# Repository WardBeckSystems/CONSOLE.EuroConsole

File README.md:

# EuroConsole

**A modular analog mixing console in Eurorack: Ward-Beck Systems circuits, digitally controlled, wired with Quad Twisted Pair.**

**Start here:** [`index.html`](index.html) walks through the whole console step by step. [`EDITOR/index.html`](EDITOR/index.html) builds your configuration as a KiCad schematic.

EuroConsole grows out of the 2016|49 *Digitally Controlled Analog Surround Sound Panner* (DCASSP), built at APK audio and Ward-Beck Systems as a Seneca College technology project. That prototype showed one idea: **the audio stays analog, the controls go digital**. Every control a mixer touches (encoders, buttons, faders, LEDs) is read by a microcontroller. The microcontroller sets digitally controlled analog parts, such as the Maxim DS1882 log-taper audio potentiometers, which do the actual work on the signal. Because the panel never carries audio, the controls can move, light up, recall and be driven remotely, and the signal path keeps the sound of the Ward-Beck circuits.

EuroConsole turns that prototype into a whole console, built from 3U Eurorack modules. The first build is the **C1616**:

| Part | What it is |
|---|---|
| **C1616 console** | 16 input channels (B300 Brain + F300 Fader strips) feeding **16 summing amplifiers**, in 4 rows of 6 modules |
| **Input** | M480B input module: the channel's mic/line front end |
| **4-input summing console** | one row: 4 × RJ45 QTP in (all 16 channels) → 4 summing amps, each with an insert point |
| **Processing** | EQ, compressor, de-esser, gate: patch into any insert |
| **Patch bay** | QTP patch bay module: inserts and buses on RJ45, normalled through |
| **Big VU Meter** (RD87) | the console's meter: the RD87 stereo Neopixel LED tower and its driver (REV 5, 2021\|54), plus moving-coil VU panels |

Everything connects with **QTP (Quad Twisted Pair)**: four balanced analog channels on one RJ45 / CAT5e cable, in the colour order **SUN, SKY, GRASS, EARTH**.

---

## How it fits together

```mermaid
flowchart LR
  subgraph CH["C1616: 16 channel strips"]
    direction TB
    B["B300 Brain<br/>input select · 4 aux · ESP32-S3"] --- F["F300 Fader<br/>POS pan · ONLY · SEL · fader · CH ON"]
  end
  IN["16 inputs<br/>(4 × QTP RJ45)"] --> M480["M480B input modules"] --> CH
  PB["QTP patch bay"] -.-|"normalled inserts and buses"| INS
  CH -->|"16 channels = 4 × QTP, to every row"| SUM
  subgraph SUM["Summing: 4 rows × (4 summing amps + insert + Big VU) = 16 summing amps"]
    direction TB
    Q["each row: 4 × RJ45 QTP in"] --> BUS["4 summing amps per row<br/>SUN · SKY · GRASS · EARTH"]
    BUS --> INS["insert point per bus<br/>send / return"]
  end
  INS <-->|"QTP send / return"| PROC
  subgraph PROC["Processing (any insert)"]
    direction TB
    EQ["EQ"] ~~~ COMP["Compressor"] ~~~ DES["De-esser"] ~~~ GATE["Gate"]
  end
  INS --> OUT["4 bus outputs (QTP)"]
  OUT --> DRV["Big VU Meter driver<br/>line in · MCU"] --> VU["Big VU Meter<br/>2 × 57 Neopixels"]
```

### Signal rules

- **Audio is analog and balanced end to end**: THAT 1246 line receivers in, THAT 1646 line drivers out. The 2016|49 prototype used these on every board.
- **Control is digital**: one ESP32-S3 per channel strip reads the panel and sets the gain parts. The modules talk to each other over I2C on the Eurorack bus, and the console talks to the outside world over the network. The 2016|49 prototype used Ethernet and the HUI protocol, run from an Arduino Mega.
- **Every interconnect is QTP**: one RJ45 carries four channels, so 16 outputs need only four cables. A QTP pair is also the insert send / return.

---

## 1. The C1616 console (16 × 16): channel strip = B300 + F300

**C1616** = 16 input channels × 16 summing amplifiers.

Each channel strip is two 6HP × 3U modules from the *HUI front panel REV 4.1* drawing ([DXF](MECHANICAL/HUI%20front%20panel%20REV%204.1.dxf)):

| B300 **Brain** (left) | F300 **Fader** (right) |
|---|---|
| INPUT LED and SEL button | **POS** encoder: position in the surround field (L · C · R · Ls · Rs) |
| SUN / SKY / GRASS / EARTH: four auxiliary controls, each with an encoder, a Neopixel and a push-button | **ONLY**: solo, isolate and cue |
| carries the channel's microcontroller | **SEL**: select, which draws attention to the channel |
| | 60 mm linear **fader** (Bourns PTA6043): channel level |
| | **CH ON**: channel on |

**Panning (from the 2016|49 theory of operation).** The POS encoder indexes a table of DS1882 settings, one per speaker, at 1 dB per step. Each speaker peaks at 63–64 steps, and neighbouring speakers cross at 48 steps (16 dB down):

```
{64,0,0,0,0} {48,48,0,0,0} {0,63,0,0,0} {0,48,48,0,0} {0,0,63,0,0} {0,0,48,48,0} {0,0,0,64,0} {0,0,0,48,48} {0,0,0,0,63}
```

The fader scales the looked-up row to a percentage. At power-up, every pot starts at full mute.

**C1616.** 16 input channels feed 16 summing amplifiers. The 16 channels leave the strips on four QTP cables (4 channels each), and every summing row receives all four. 16 strips × 12HP = 192HP, which is three rows of 84HP.

---

## 2. Summing: 4 rows of 6 = 16 summing amplifiers

The summing side is **4 rows of 6 modules**. Each row is one **4-input summing console**:

| Slot | Module |
|---|---|
| 1–4 | **summing amplifiers**: the row's four buses, SUN · SKY · GRASS · EARTH. All 16 channels arrive on the row's 4 × RJ45 QTP inputs |
| 5 | **insert / patch**: an insert send / return for each of the row's four buses (QTP) |
| 6 | **Big VU (RD87)**: meters the row's four buses |

4 rows × 4 = **16 summing amplifiers**: 16 inputs × 16 summing buses. Each bus has an **insert point** and leaves on a QTP output. *Slots 5 and 6 are provisional; the layout of 4 summing amps + 2 per row is set.* Big VU REV 5 shows two bars, so the row needs a 4-bar version, or two towers.

- **Summing amplifier:** Ward-Beck [M450](https://github.com/WardBeckSystems/MODULES.AMPLIFIERS.M450-Program-Summing-Amplifier) / [M450A](https://github.com/WardBeckSystems/MODULES.AMPLIFIERS.M450A-Program-Summing-Amplifier) / [M450B](https://github.com/WardBeckSystems/MODULES.AMPLIFIERS.M450B-Program-Summing-Amplifier) program summing amplifiers (Rodger Beck, 1975|8–1979|12). The 2016|49 prototype summed through 2 × 4 M450A cards. Also [M484 Dual Summing Amplifier](https://github.com/WardBeckSystems/MODULES.SUMMING.M484-Dual-Summing-Amplifier).
- **QTP backplane:** **QTP-BAC 14.1** (in `KICAD/`) is the four-channel QTP board, with RJ45s, transformers, XLR and BNC for SUN/SKY/GRASS/EARTH. It is the starting point for the summing console's input/output board.
- **Insert points:** a balanced send and return per bus, switched in or out. The model is the [M499 Insertion Switcher](https://github.com/WardBeckSystems/MODULES.UNSORTED.M499-Insertion-Switcher), plus the 1979|12 *M466N Insert Meter Module* drawing ([M466](https://github.com/WardBeckSystems/MODULES.DYNAMICS.M466-Limiter-Compressor-Module)). *Proposed:* sends on one RJ45 and returns on another, with QTP pairs 1–4 = buses 1–4, so one cable pair inserts a processor into all four buses.

---

## 3. Input: M480B

The [M480B input module](EAGLE/2021-APK/M480B%20Input%20module.sch) is the channel front end ahead of the B300/F300 strip. APK redrew it in Eagle in 2021|54 from the Ward-Beck original: LM201 op-amps, a MAT-01 matched pair and discrete output transistors (255 parts).

## 4. Processing: EQ, compressor, de-esser, gate

Each processor is a Eurorack module with QTP send / return, so it patches into any insert. Each one starts from a Ward-Beck circuit already drawn in this archive. Three already exist as 2021|54 APK Eagle redraws in [EAGLE/2021-APK](EAGLE/2021-APK/):

| Function | Starting from | Eagle (2021\|54 APK) | KiCad in the archive |
|---|---|---|---|
| **EQ** | [M462B Effects Equalizer](https://github.com/WardBeckSystems/MODULES.FILTERS.M462B-Equalizer-Module); also [M462](https://github.com/WardBeckSystems/MODULES.FILTERS.M462-Equalizer-Module), [M472](https://github.com/WardBeckSystems/MODULES.FILTERS.M472-Equalizer-Module) / [M472A](https://github.com/WardBeckSystems/MODULES.FILTERS.M472A-Stereo-Equalizer-Module) | `M462B Final.sch` (356 parts) | M462 27 · M462B 10 · M462C 11 · M472 14 · M472A 7 sheets |
| **Compressor** | [M466 Limiter-Compressor](https://github.com/WardBeckSystems/MODULES.DYNAMICS.M466-Limiter-Compressor-Module) (1976\|9): signal path, 6-106 control amplifier, output amplifier | `M466-compressor-limiter.sch` (315), `M466 - Control amp.sch` (114) | M466 15 · [M466M](https://github.com/WardBeckSystems/MODULES.DYNAMICS.M466M-Compressor-Meter-Module) 3 |
| **Output amplifier** (EQ and compressor) | the M466 / M462B output stage: LM201 and 4 complementary pairs | `M466 and M462B Output Amplifier.sch` (87) | in M466 |
| **De-esser** | M466 with a frequency-weighted (high-pass / band-pass) side-chain into its control amplifier | — | new circuit, based on M466 |
| **Gate** | [M467 Noise Gate and Meter Module](https://github.com/WardBeckSystems/MODULES.DYNAMICS.M467-Noise-Gate-and-Meter-Module) | — | M467 8 |

The front panels follow the B300/F300 language: encoders with Neopixels and POD buttons. The processor's ESP32-S3 sets its thresholds and gains through digitally controlled parts.

## 5. Patch bay

The **QTP patch bay module** puts every insert send / return and bus on RJ45, normalled through, so processors patch in with one CAT cable per four channels. It starts from **QTP-BITTREE PATCHBAY REV 2.1** (2021|54, Gerbers marked "good to go"): a 34 × 41 mm card with a top-row and bottom-row QTP RJ45, plugging into a Bittree patchbay connector, so a Bittree bay becomes a QTP bay. A sibling, **QTP-NEUTRIK D-hole** (24 × 27 mm), mounts a QTP RJ45 in a standard Neutrik D-hole for panels.

## 6. Metering: the Big VU Meter (RD87)

Big VU is Ward-Beck R&D project **RD87**, the *RD87 LED tower* (2015|48): a free-standing stereo level tower. Product repo: [PRODUCTS.BigVU](https://github.com/WardBeckSystems/PRODUCTS.BigVU). Page: [WBSps.ca Big VU](https://WBSps.ca/2026/PAGES/Big-VU.html). Simulator: [Big VU](https://WBSps.ca/2026/siumulation.html?plugin=bigvu), with front panel, tutorial, block diagram and firmware trace. In EuroConsole it is the console's meter bridge: one tower per bus pair, fed from the bus outputs.

- **VU meter driver + meter: Big VU Meter REV 5** (2021|54, 102 × 64 mm). A dual op-amp line input feeds an Arduino Micro, which drives two Neopixel bars of 57 pixels each (left / right). Two WBS 10-080 pots set the ceiling. The firmware ([SOFTWARE/BigVU](SOFTWARE/BigVU/), 2015|48) adds a log scale, calibration and two falling peak dots. This is the driver to move to Eurorack and the ESP32-S3.
- **Moving-coil VU meters**, one per bus, as in the 2016|49 prototype (five WBS meters, each with a 15 dB calibration pad): [M435 VU Meter](https://github.com/WardBeckSystems/MODULES.METER.M435-VU-Meter), driven by an [M405 Extended Range VU Meter](https://github.com/WardBeckSystems/MODULES.METER.M405-Extended-Range-VU-Meter) / [M445](https://github.com/WardBeckSystems/MODULES.METER.M445-Extended-Range-Meter) stage (+4 dBu = 0 VU).

---

## Console editor: configuration → KiCad schematic

[`EDITOR/index.html`](EDITOR/index.html) is an interactive page that builds a specific console and writes its KiCad 9 schematic. Open it in a browser; it works offline from the file.

- **Every Eurorack module is a bank of 4 channels** (one QTP in / out): quad preamp (4 preamp sections + 4 vertical VU), EQ, compressor, de-esser, send banks and faders, 24HP, drawn to Eurorack scale with the master section in the middle.
- **Summing in the send banks:** each send bank (Aux 1-4, Aux 5-8, M 1-4) takes two 4-channel inputs, PRE (the insert return, before the fader) and POST (the fader out), sets every send pre or post, sums its 4 channels per bus inside the module with the bus coming in from the previous bank, and passes the bus on to the next bank, then the master (insert, compressor, fader, Big VU). No summing point takes more than 5 inputs. Every bank also has a pre-fader and a post-fader QTP out. Separate summing amps are set aside for now.
- **Digitally controlled analog:** every parameter is a DS1882 wiper or a digital switch under a control layer (an ESP32-S3 per bank on I2C). The editor counts the parameters, DS1882s, I2C expanders and I2C buses.
- **Power:** a first estimate per module on +12 V, −12 V and +5 V, per rack row and in total, with the supplies needed and a power-flow diagram (to be measured).
- **Summing rows:** each summing amp is a bus named by what it sums: M1–M4, AUX1–AUX8, then direct sums (BUS13…). The C1616 is rows M1–4 · AUX1–4 · AUX5–8 · BUS13–16, each with insert and Big VU. The name follows the configuration: 16 inputs × 16 summing amps = **C1616**.
- **Download:** a zip of a hierarchical KiCad 9 project: a root sheet, a channels sheet and one sheet per summing row. It includes `EuroConsole.kicad_sym` and `sym-lib-table`, plus the configuration (JSON, which *Load config* reads back) and a parts list (CSV).
- **Symbols:** the Ward-Beck modules use the archive's own symbols (`2026/Engineering/KICAD`: M480B, M450, M499, M462B, M466, M467), with their real card-edge pins. QTP RJ45, XLR, the B300/F300 strip and the RD87 Big VU are EuroConsole parts. Run `python3 EDITOR/build_symbols.py` to refresh `symbols.js`.
- **Nets** are global labels shared by every sheet: `IN` (XLR), `FS`/`FR` (M480B fader send / return through the strip), `CH` (channels on QTP), `SUMN` (summing nodes), `SEND`/`RET` (inserts), `BUS` (bus outputs) and `P<ref>_` (processor patch points). QTP pairs are SUN 2/1 · SKY 4/5 · GRASS 6/3 · EARTH 8/7, with the shell to GND.
- **Tested:** `node EDITOR/test_generator.js` generates the C1616, has `kicad-cli` load it, and checks the netlist. Each summing node has its 16 resistors plus the M450 input; each channel reaches its 16 resistors and all four rows. ERC leaves only "power pin not driven" (the schematic has no supply). The archive's M462B, M466 and M467 symbols give left and right the same pin numbers, so ERC reports duplicate pins when those modules are placed.

## Reference: Boredbrain Xcelon

The [Boredbrain Music Xcelon](https://www.chicagomusicexchange.com/en-ca/blogs/news/boredbrain-music-xcelon-eurorack) (CA$1,372) is the closest commercial Eurorack mixer: an all-analog six-channel stereo mixer in one module. Its features, against EuroConsole:

| Xcelon | EuroConsole |
|---|---|
| Six stereo / dual-mono channels, low-noise analog | banks of 4 mono channels per module; balanced +4 dBu on QTP; Ward-Beck circuits |
| Two stereo FX sends, two FX returns | Aux 1-4 and Aux 5-8 send banks (8 sends); returns through the insert / patch bay |
| Two stereo mix buses, selectable per channel | M 1-4 send bank onto the M1-M4 masters; direct sums |
| Variable input gain for modular and line-level sources | quad preamp (M480 / M460 / M470 / M441): mic or line; **planned:** a Eurorack-level input setting |
| Long-travel faders with CV-responsive LEDs | F300 fader bank (60 mm Bourns) with Neopixels |
| Balance with pan law; dual-mono crossfade mode | F300 POS pan on the DS1882 pan-law table; **planned:** crossfade mode |
| Clickless mutes, VU meters on all channels | CH ON; the DS1882's zero-crossing detector switches without clicks; quad preamp meters and Big VU on every bus |
| 26 CV inputs | **planned:** CV in per channel (volume 0 to +5 V, pan ±5 V, sends), read by the bank's ESP32-S3 |
| Jumpers: pre/post-fader FX and meters, volume VCA mode | send taps are post-fader (in software, settable per bank, **planned**); every level is a DS1882, so a VCA mode is a firmware setting |
| Expansion ports: channel expanders, direct outs | every bank is a module; every channel already leaves on QTP (direct out) |

## Reference: XAOC Devices Praga

The **XAOC Devices Praga** (*1967 Voltage Controlled Stereo Mixing Console*) is a Eurorack mixer laid out the way EuroConsole lays out every module: **a bank of 4 channels in one module**. From its front panel, each channel has a large VOL knob, an ACTIVE / MODE button with a status LED, PAN, an AUX knob between sends A and B, a **5-segment vertical LED meter**, and jacks for INPUT, VCA OUT and PAN / VOL CV; the shared row carries AUX SEND / RETURN A and B and the STEREO SUM L / R.

| Praga | EuroConsole |
|---|---|
| 4 channels per module | every module is a bank of 4 channels (24HP, one QTP in and out) |
| a vertical LED meter per channel | the quad preamp's vertical VU per channel; Big VU on every bus |
| PAN and VOL CV per channel | **planned** (see the Xcelon: CV in, read by the bank's ESP32-S3) |
| AUX knob between sends A and B | the send banks: Aux 1-4, Aux 5-8, M 1-4 |
| VCA OUT per channel | every channel leaves on QTP (direct out) |
| stereo sum on the module | summing stays in its own modules: group sums of 8 with their channels, the Σ in the master |

## Reference: WMD Performance Mixer MKII

The **WMD Performance Mixer MKII** (US$2,205; PM Channels MKII US$955, PM DB25 MKII US$440, PM MKII Returns US$205) is the most console-like of the three: eight stereo channels, expanding **four channels at a time** up to 24.

| Performance Mixer MKII | EuroConsole |
|---|---|
| Expands 4 channels at a time (PM Channels MKII), up to 24 | every module is a bank of 4; channels in fours, 4 to 64 |
| DB25 MKII: balanced line-level outs, pre- or post-fader, per 4 channels | every bank leaves on QTP (4 balanced channels per RJ45); **planned:** pre / post choice |
| Gain −12 to +20 dB, clip LED 1 dB before clipping | quad preamp gain; **planned:** a clip LED per channel |
| Soft mute (no click) | CH ON through the DS1882's zero-crossing switch |
| Pan or crossfade per channel; CV sums with the pot | F300 POS pan; **planned:** crossfade mode and CV in |
| Faders as VCAs (Level CV in VCA mode) | every level is a DS1882 set by the ESP32-S3: a VCA mode is firmware |
| AUX1 post, AUX2 pre or post | Aux 1-4 / Aux 5-8 send banks, post-fader; **planned:** pre / post per bank |
| Cue and Bus: master only, master + bus, bus only | ONLY (solo / cue) on the F300; M 1-4 send bank onto the M1-M4 masters |
| Groups: 8 mute / bus / cue snapshots recalled with one hand | **planned:** snapshots in the ESP32-S3s (the controls are all digital already) |
| Master insert; Mix In after the insert; Aux returns before it | insert on every master bus (M499 + QTP send / return); **planned:** a Mix In after the master insert |
| Balanced stereo master out, LED VU | QTP bus outs; Big VU on every bus |
| Replaceable channel strips; patchbay, power and master as separate assemblies | every bank module is replaceable by itself |
| Expansion headers 2.0 mm shrouded, cannot be plugged into power | **planned:** keyed inter-module connectors that cannot meet the Eurorack 16-pin power |

**From the manual** (WMD, *Performance Mixer MKII*):

| | Performance Mixer MKII | PM Channels MKII (4 ch) | DB25 MKII |
|---|---|---|---|
| Width | 52HP | **24HP** | 4HP |
| Power | +620 / −560 mA (to ±750 mA when distorting) | +320 / −280 mA (to ±350 mA) | ±150 mA |
| Inputs | 20 kΩ; HPF −3 dB at 10 Hz; gain −12 to +20 dB | same | — |
| Faders / aux | −100 to +5 dB; level / aux CV 0 to 5 V (100 kΩ); pan CV ±5 V (200 kΩ) | same | — |
| Outputs | master balanced 3.5 mm TRS, 600 Ω, DRV135; others 1 kΩ modular level | 1 kΩ modular level | 16 × DRV135, balanced 600 Ω, **+4 dBu nominal**, THD+N < 0.1 %, TASCAM DB25 |
| Pan law | −3 dB centre, −100 / 0 dB hard pan | same | — |
| Response | ±0.5 dB 20 Hz–20 kHz; L/R within ±0.5 dB; every point phase-correct | same | — |

Also from the manual:
- Each OUTS header is 2 mm, 16-pin: four stereo channels, signal on the even pins and ground on every odd pin.
- Each INSERT header is 8-pin: send / return left and right, post-gain and pre-fader, with jumpers when unused.
- MIDI: CC 32 upward, 4 per strip (level, pan, aux 1, aux 2).
- 8 group snapshots of mute, bus and cue.
- Firmware loads from an SD card.

**What it tells EuroConsole:**
- **Width:** a bank of 4 at 24HP is what WMD ships for 4 channels (PM Channels MKII).
- **Power:** about +320 / −280 mA per 4-channel module is a realistic budget to check our banks against on ±12 V.
- **Balanced outs:** WMD's DB25 uses DRV135 drivers at +4 dBu. Our THAT 1646 drivers do the same job on QTP.
- **Internal ribbons:** ground on every other conductor between modules.
- **Inserts:** an insert point on every channel, post-gain and pre-fader, beside the master insert.
- **Firmware:** the ESP32-S3s can send the same kind of MIDI CC overlay for DAW automation, and keep group snapshots.

## Boards in this repo

`KICAD/` holds KiCad 9 boards converted from the Eagle designs in `EAGLE/` with [`tools/eagle2kicad_pcb.py`](https://github.com/WardBeckSystems/WBSps.ca/blob/main/tools/eagle2kicad_pcb.py). `KICAD/split_boards.py` splits the combined 2016|49 Eagle sheet into one board per module. Each board is placed in its panel's coordinates, with the panel drawing on *User.Drawings*.

| Board | From | Size | Parts | Panel check |
|---|---|---|---|---|
| `B300_Front` | 2016\|49 Encoder PCB 17.2 | 30 × 113.6 mm | 37 | all 14 controls within 0.18 mm of their panel holes (4 Neopixels + INPUT LED, 4 encoder holes, 5 buttons) |
| `F300_Fader` | 2016\|49 Encoder PCB 17.2 | 30 × 113.6 mm, L-shape | 14 | ONLY, SEL and CH ON within 0.01 mm; the fader's 4 mounting pads within 0.02 mm of the panel screws; the POS encoder mounts on the panel above the notch |
| `B300_Main` | 2016\|49 Encoder PCB 17.2 | 133.8 × 113.4 mm | 27 | perpendicular side board: 4 encoders (WBS 10-081), Arduino Mega, RS-485, DB9, DS1808 |
| `Maxim_Adapter_Board` | 2016\|49 Maxim Adapter Board | 20 × 25 mm | 3 | DS1882 breakout (also on the Encoder sheet) |
| `QTP-BAC_14.1` | 2016\|49 | 114 × 50 mm | 112 | four-channel QTP backplane: RJ45, transformers, XLR, BNC |
| `Big_VU_Meter_REV5` | 2021\|54 APK | 102 × 64 mm | 84 | stereo Neopixel VU meter and driver |
| `QTP-BITTREE_Patchbay_REV2.1` | 2021\|54 APK | 34 × 41 mm | 10 | QTP card for a Bittree patchbay |
| `QTP-NEUTRIK_D-hole` | 2021\|54 APK | 24 × 27 mm | 7 | QTP RJ45 in a Neutrik D-hole |
| `Encoder_PCB_17.2` | 2016\|49 | — | 221 | the whole Eagle sheet, kept as the source |

| B300 Front | F300 Fader | Big VU Meter | QTP Bittree patchbay |
|---|---|---|---|
|  |  |  |  |

**Schematics.** The Eagle `.sch` files (M480B, M462B, M466, the output amplifier, the VU meter, the patchbay, and the 2016|49 DCASSP sheets) still need KiCad's GUI importer: File → Import → Non-KiCad Schematic. The 2016|49 schematics are also in [MANUALS/2016 - DCASSP schematics V1.pdf](MANUALS/2016%20-%20DCASSP%20schematics%20V1.pdf).

## Roadmap

- **From the Xcelon, the Praga and the WMD Performance Mixer MKII:** CV inputs per channel (volume, pan, sends) read by each bank's ESP32-S3; a Eurorack-level input setting and a clip LED per channel on the quad preamp; pan crossfade mode; pre / post-fader sends and direct outs per bank; mute / bus / cue snapshots; a Mix In after the master insert; keyed inter-module connectors that cannot meet power.

1. **B300 / F300 for Eurorack**: replace the Arduino Mega side board with an ESP32-S3 on the B300, and connect the F300 by ribbon. Use the Eurorack 16-pin power header (±12 V, regulated to ±7 V for the DS1882 analog rails). Connect modules over I2C.
2. **Input**: M480B as a Eurorack input module.
3. **Summing console**: a 4 × QTP input board from QTP-BAC, an M450-style summing amplifier per bus, and an insert send / return per bus.
4. **Processing**: EQ (M462B), compressor (M466), de-esser (M466 side-chain), gate (M467). Each gets a Eurorack PCB and panel with QTP send / return, sharing the M466/M462B output amplifier.
5. **Patch bay**: QTP-BITTREE and QTP-NEUTRIK into a Eurorack QTP patch module, normalled.
6. **Metering**: Big VU Meter onto the ESP32-S3 as the VU meter driver, plus moving-coil VU panels.
7. **The C1616 frame**: three 84HP rows, the power, the QTP patch, and network control.

## Source material

| Folder | What |
|---|---|
| [EAGLE/2016-DCASSP](EAGLE/2016-DCASSP/) | Encoder PCB 17.2, QTP-BAC 14.1, Maxim (DS1882) adapter, VU meter and summing amp, block diagram |
| [EAGLE/2021-APK](EAGLE/2021-APK/) | M480B, M462B, M466, M466 control amp, M466/M462B output amp, Big VU Meter REV 5, QTP-BITTREE patchbay, QTP-NEUTRIK D-hole |
| [GERBERS/](GERBERS/) | QTP-BITTREE PATCHBAY REV 2.1 ("good to go") |
| [SOFTWARE/](SOFTWARE/) | DCASSP channel-strip firmware (Arduino Mega, 2016) with its history, pan law and PC interface; Big VU meter firmware (all versions), which runs every vertical meter |
| [MANUALS/](MANUALS/) | 2016\|49 DCASSP final report (TPJ655) and schematics |
| [MECHANICAL/](MECHANICAL/) | HUI front panel REV 4.1 (DXF and render), Bourns PTA6043 fader |
| [PHOTOS/](PHOTOS/) | HUI prototype cross reference |

---
© Ward-Beck Systems (Ward-Beck.com - Ward-Beck.ca) · DCASSP design and archive by Anthony Peter Kuzub · [WBSps.ca](https://WBSps.ca) · [WBSps.Kuzub.com](https://WBSps.Kuzub.com)

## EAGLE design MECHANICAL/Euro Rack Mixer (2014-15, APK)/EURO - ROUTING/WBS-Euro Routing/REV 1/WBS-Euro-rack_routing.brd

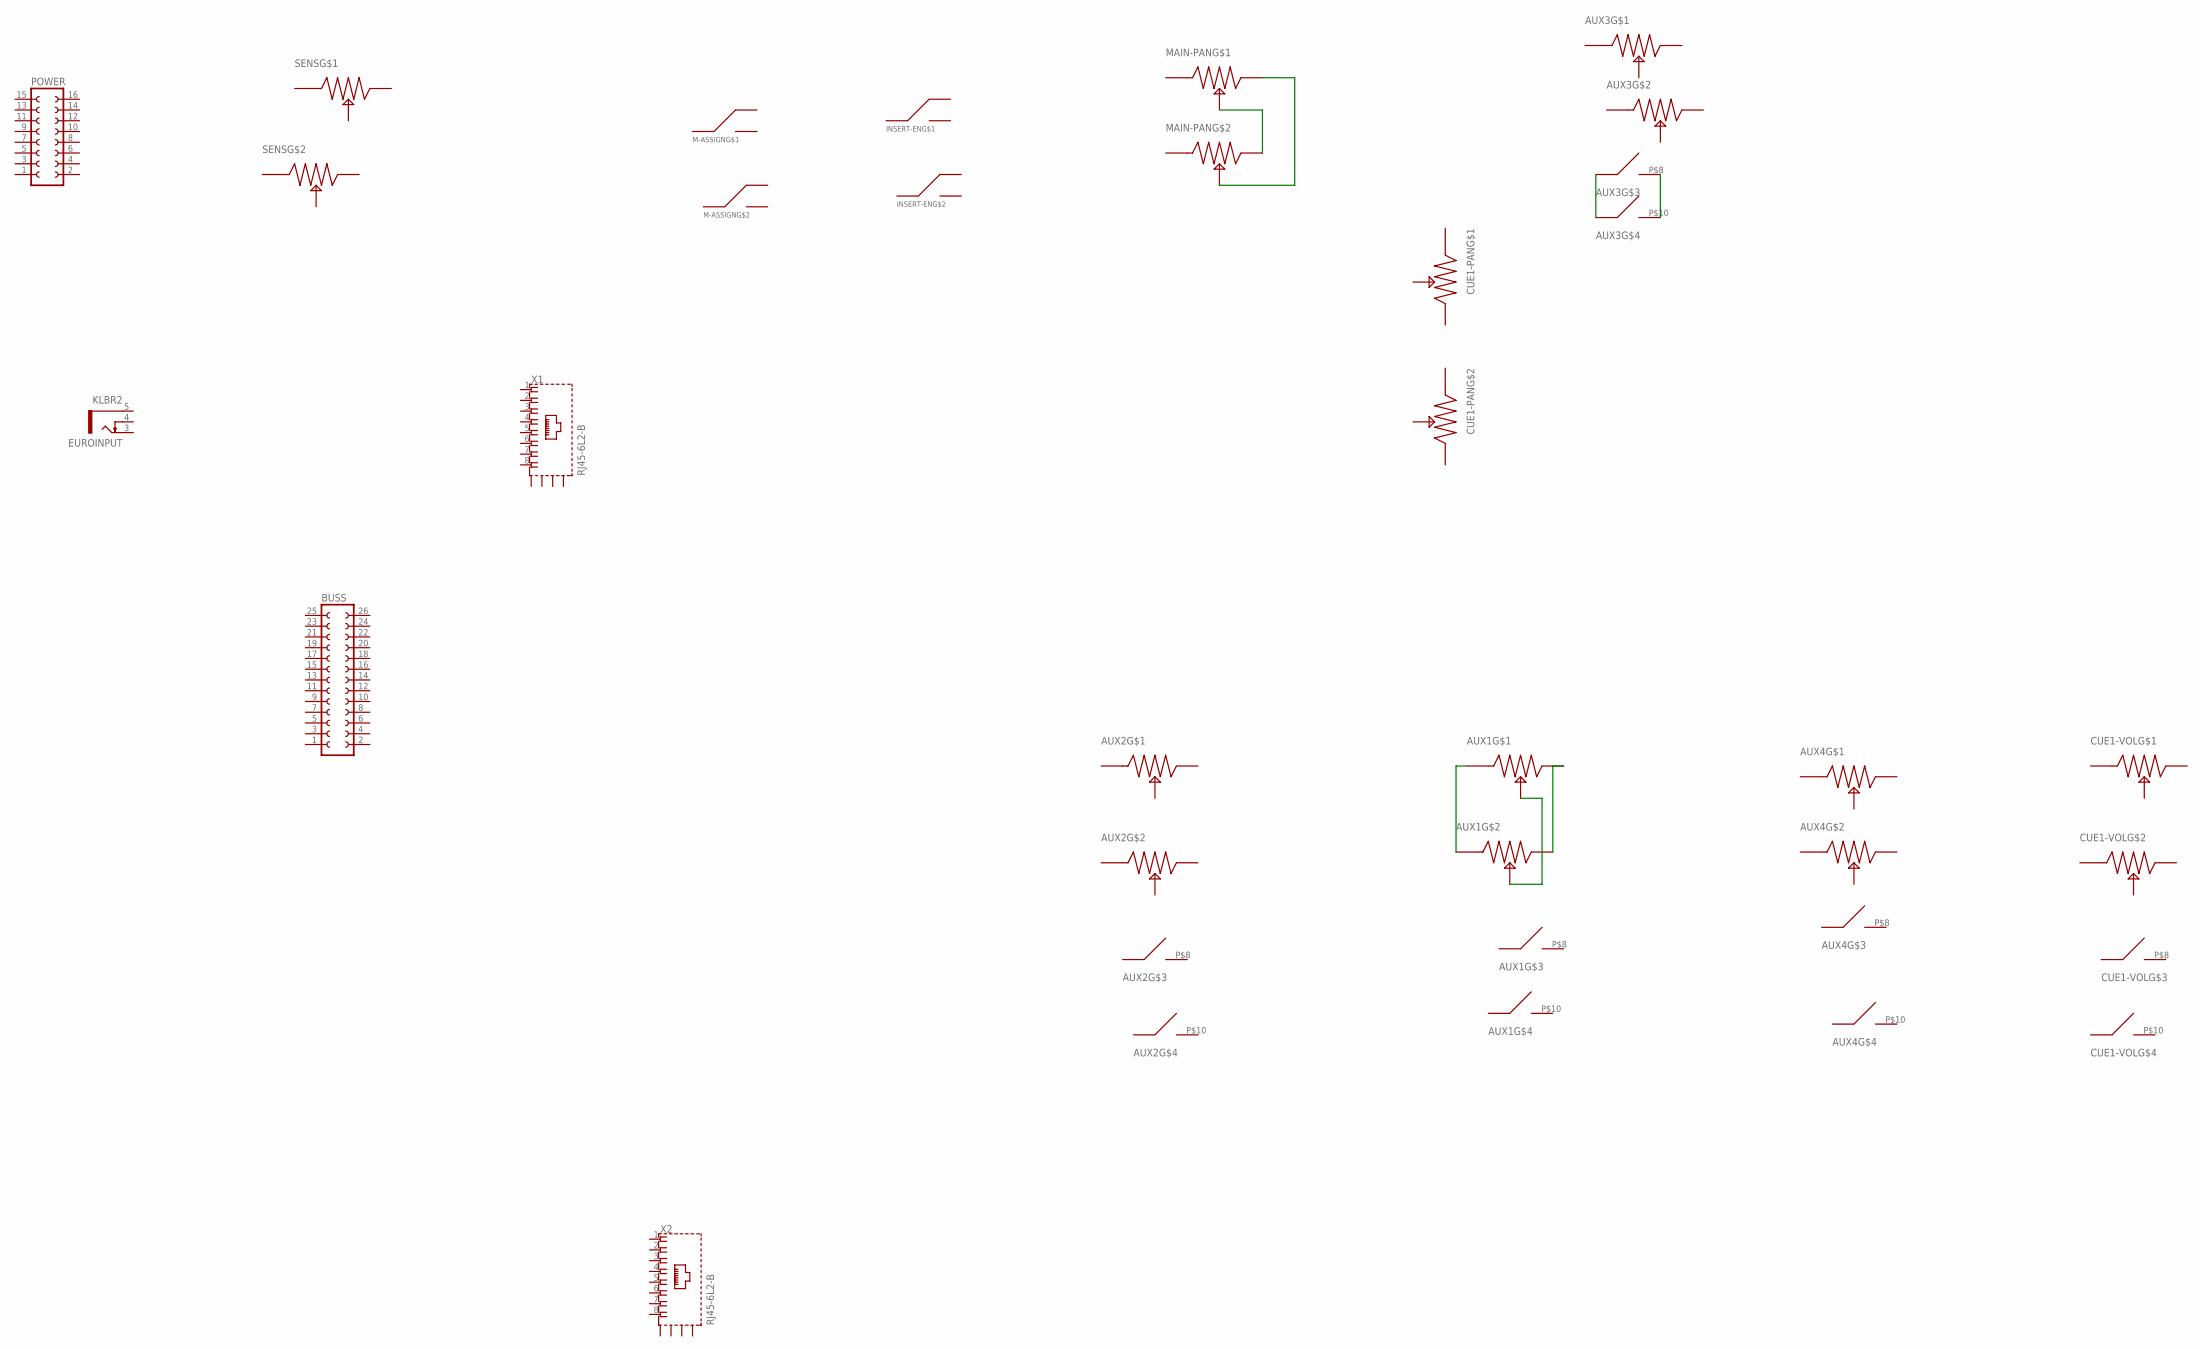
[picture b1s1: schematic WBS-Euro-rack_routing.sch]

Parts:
AUX1, AUX2, AUX3, AUX4: WBS_10-081_DUALPOT+DUALSWITCH; WBS_10-081
BUSS: FE13-2
CUE1-PAN: WBS_10-079_POT; WBS_079
CUE1-VOL: WBS_10-081_DUALPOT+DUALSWITCH; WBS_10-081
EUROINPUT: KLBR2
INSERT-EN: WBS_DPDT; WBS_DPDT_SWITCH
M-ASSIGN: WBS_DPDT; WBS_DPDT_SWITCH
MAIN-PAN: WBS_10-079_POT; WBS_079
POWER: FE08-2
SENS: WBS_10-079_POT; WBS_079
X1, X2: RJ45-6L2-B; RJ45-SHIELD2

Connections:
unnamed: MAIN-PAN.P$3 (CW), MAIN-PAN.P$5 (WIPER)
unnamed: MAIN-PAN.P$2 (WIPER), MAIN-PAN.P$6 (CW)
unnamed: AUX3.P$7, AUX3.P$9
unnamed: AUX3.P$8, AUX3.P$10
unnamed: AUX1.P$3 (CW), AUX1.P$6 (CW)
unnamed: AUX1.P$1 (CCW), AUX1.P$4 (CCW)
unnamed: AUX1.P$2 (WIPER), AUX1.P$5 (WIPER)

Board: 2 copper layers, 15 parts (4 on the bottom side), 7 nets, no tracks yet.

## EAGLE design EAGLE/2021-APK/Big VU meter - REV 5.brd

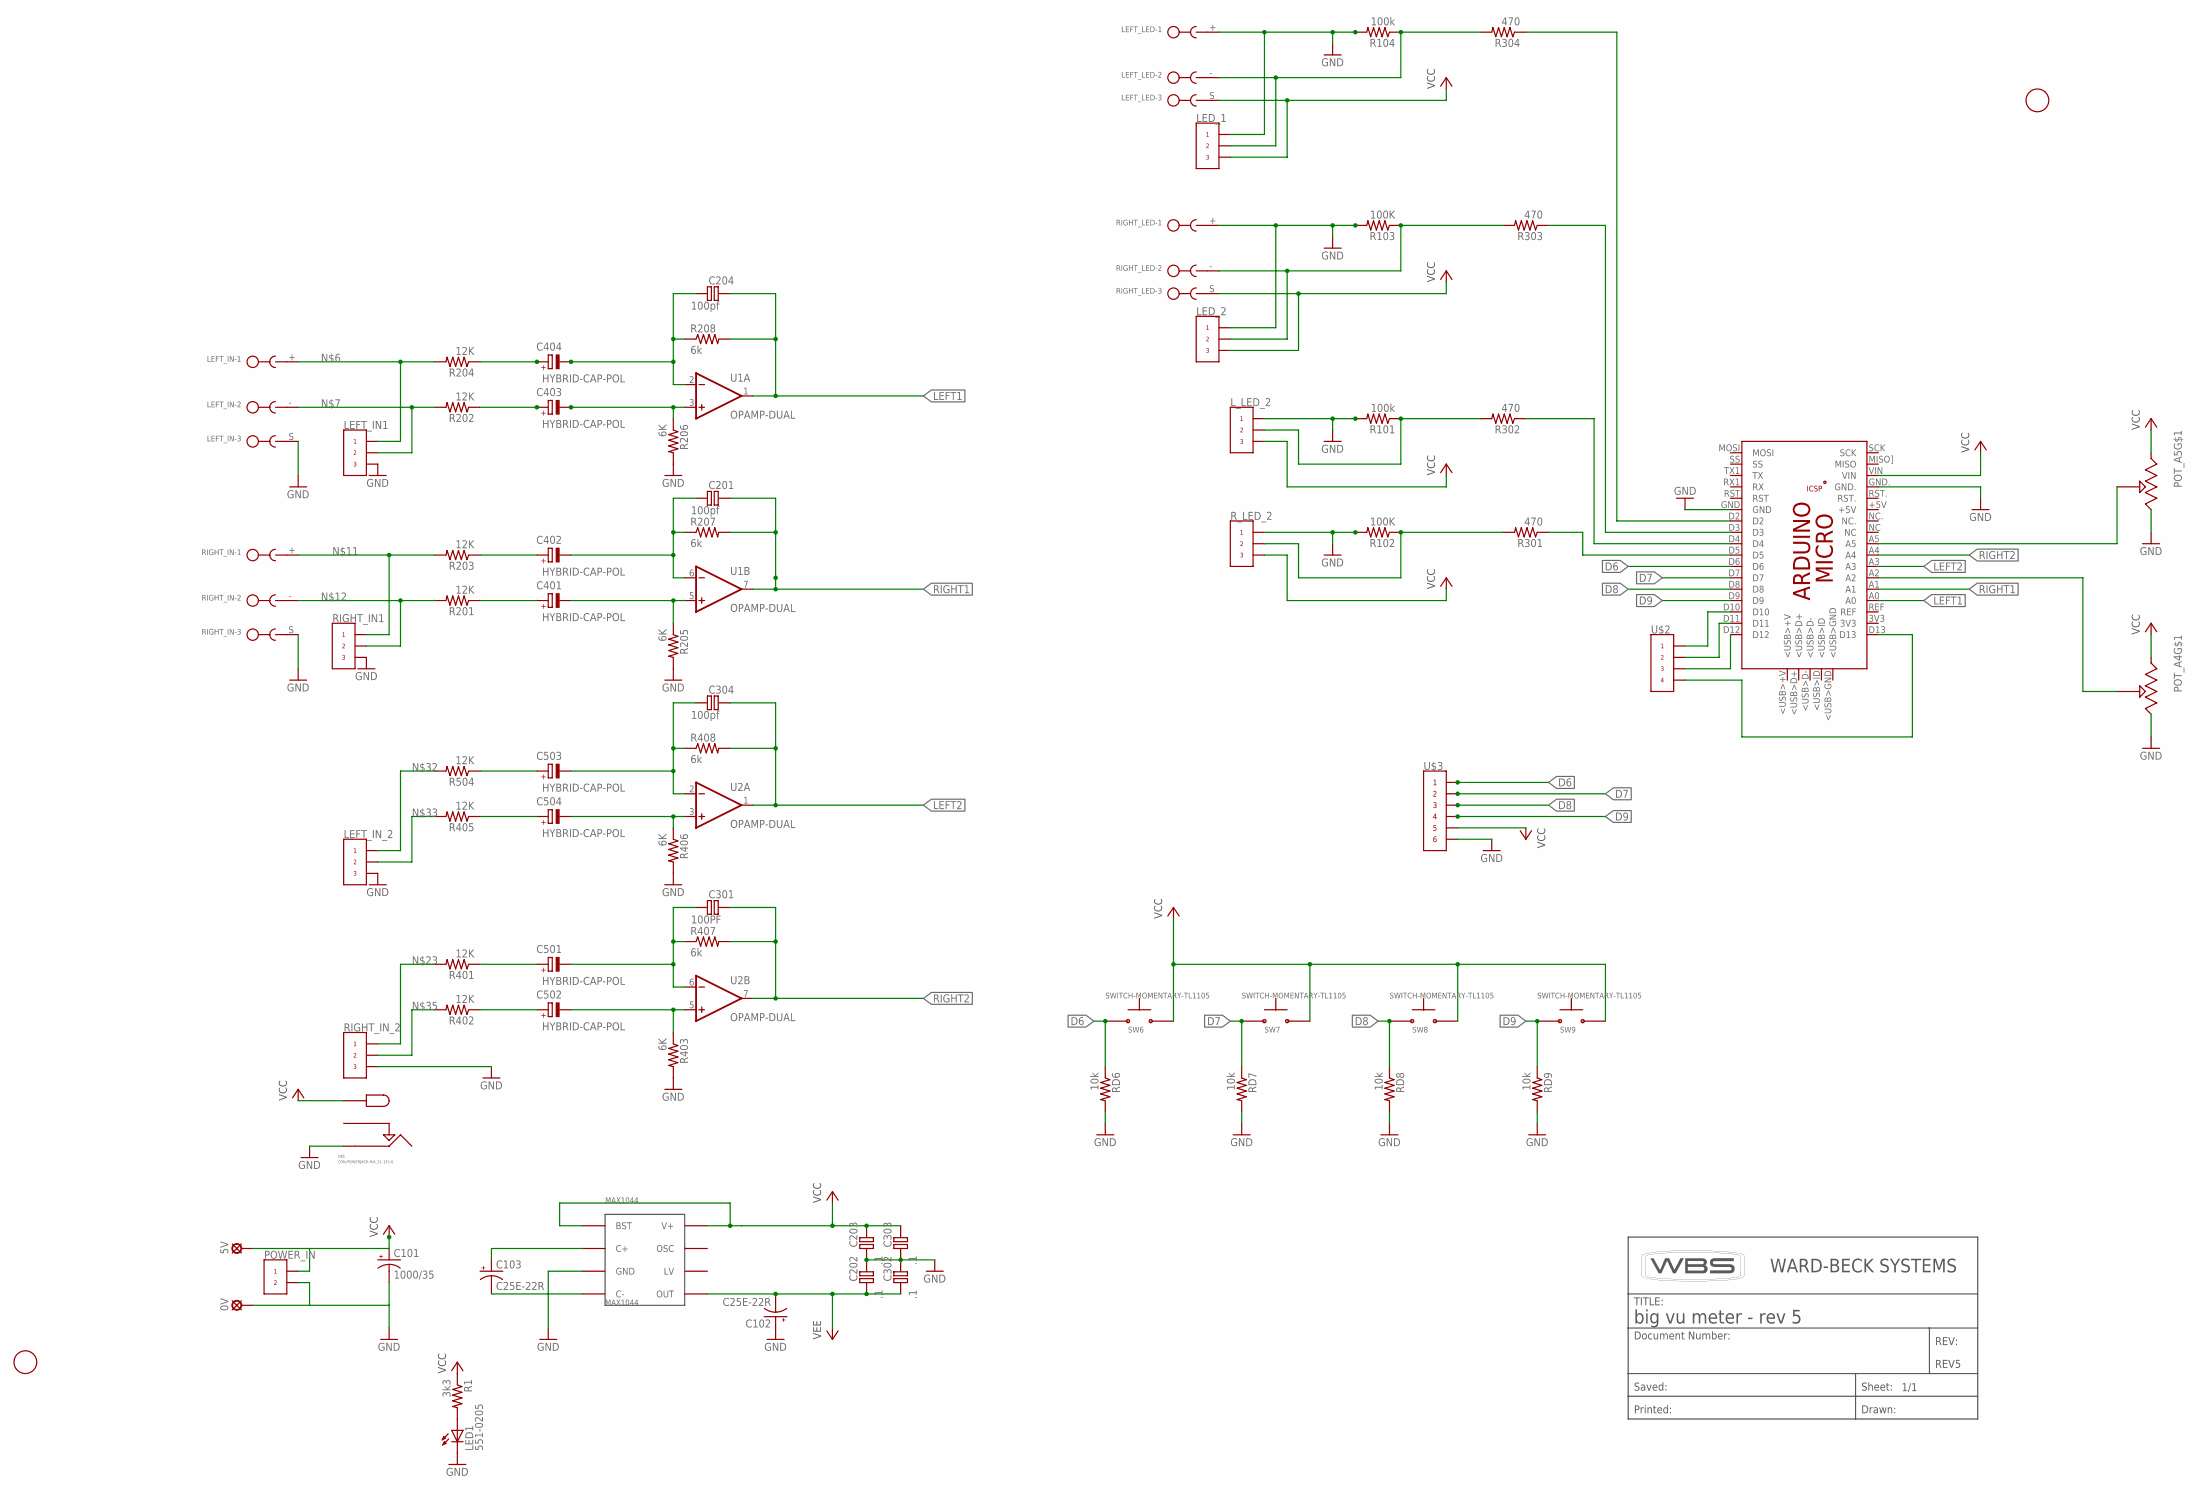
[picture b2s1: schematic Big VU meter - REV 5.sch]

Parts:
0V, 5V: LSP13
C101: 1000/35; E5-5
C102, C103: C25E-22R; E2,5-6
C201, C204, C304: 100pf; HYBRID-CAP-CERAMIC-1206
C202, C203, C302, C303: .1; HYBRID-CAP-CERAMIC-1206
C301: 100PF; HYBRID-CAP-CERAMIC-1206
C401, C402, C403, C404, C501, C502, C503, C504: HYBRID-CAP-POL; HYBRID-CAP-TANT
LED1: 551-0205; LED_LD260
LED_1, LED_2: CON-WBS-LOCKING-0.1-3
LEFT_IN: CON-PHOENIX_RIGHT_ANGLE_3.81; CON-PHOENIX_MC1.5/3-G-3.81
LEFT_IN1: CON-WBS-LOCKING-0.1-3
LEFT_IN_2: CON-WBS-LOCKING-0.1-3
LEFT_LED: CON-PHOENIX_RIGHT_ANGLE_3.81; CON-PHOENIX_MC1.5/3-G-3.81
L_LED_2: CON-WBS-LOCKING-0.1-3
MAX1044: MAX1044; DIP8
PCB1: ARDUINO_MICRO
POT_A4, POT_A5: 10-080; WBS_079
POWER_IN: CON-WBS-LOCKING-0.1-2
R1: 3k3; HYBRID-RESISTOR-1206-0.3
R101, R104: 100k; HYBRID-RESISTOR-1206-0.3
R102, R103: 100K; HYBRID-RESISTOR-1206-0.3
R201, R202, R203, R204, R401, R402, R405, R504: 12K; HYBRID-RESISTOR-1206-0.3
R205, R206, R403, R406: 6K; HYBRID-RESISTOR-1206-0.3
R207, R208, R407, R408: 6k; HYBRID-RESISTOR-1206-0.3
R301, R302, R303, R304: 470; HYBRID-RESISTOR-1206-0.3
RD6, RD7, RD8, RD9: 10k; HYBRID-RESISTOR-1206-0.3
REV5: WBS-DOCUMENT_INFO_FRAME; WBS-FRAME_PCB
RIGHT_IN: CON-PHOENIX_RIGHT_ANGLE_3.81; CON-PHOENIX_MC1.5/3-G-3.81
RIGHT_IN1: CON-WBS-LOCKING-0.1-3
RIGHT_IN_2: CON-WBS-LOCKING-0.1-3
RIGHT_LED: CON-PHOENIX_RIGHT_ANGLE_3.81; CON-PHOENIX_MC1.5/3-G-3.81
R_LED_2: CON-WBS-LOCKING-0.1-3
SW6, SW7, SW8, SW9: SWITCH-MOMENTARY-TL1105; SWITCH-TACT_TL1105
U1, U2: OPAMP-DUAL; DIP8
U$1: CON-POWERJACK-R/A_31-155-0
U$2: CON-WBS-LOCKING-0.1-4
U$3: CON-WBS-LOCKING-0.1-6
U$4, U$5: FIDUCIAL; FIDUCIAL_1MM

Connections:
D6: PCB1.D6, RD6.1, RD6.1A (1), SW6.P$1 (1), SW6.P$2 (1), U$3.P$1
D7: PCB1.D7, RD7.1, RD7.1A (1), SW7.P$1 (1), SW7.P$2 (1), U$3.P$2
D8: PCB1.D8, RD8.1, RD8.1A (1), SW8.P$1 (1), SW8.P$2 (1), U$3.P$3
D9: PCB1.D9, RD9.1, RD9.1A (1), SW9.P$1 (1), SW9.P$2 (1), U$3.P$4
D10: PCB1.D10, U$2.P$1
D11: PCB1.D11, U$2.P$2
D12: PCB1.D12, U$2.P$3
D13: PCB1.D13, U$2.P$4
GND: 0V.MP, C101.-, C102.+, C202.2 (-), C202.B2 (-), C203.1 (+), C203.A1 (+), C302.2 (-), C302.B2 (-), C303.1 (+), C303.A1 (+), LED1.K (C), LED_1.P$1, LED_2.P$1, LEFT_IN.S, LEFT_IN1.P$3, LEFT_IN_2.P$3, LEFT_LED.+, L_LED_2.P$1, MAX1044.P$3 (GND), PCB1.GND, PCB1.GND., POT_A4.P$3 (CW), POT_A5.P$3 (CW), POWER_IN.P$2, R101.2, R101.2A (2), R102.2, R102.2A (2), R103.2, R103.2A (2), R104.2, R104.2A (2), R205.2, R205.2A (2), R206.2, R206.2A (2), R403.2, R403.2A (2), R406.2, R406.2A (2), RD6.2, RD6.2A (2), RD7.2, RD7.2A (2), RD8.2, RD8.2A (2), RD9.2, RD9.2A (2), RIGHT_IN.S, RIGHT_IN1.P$3, RIGHT_IN_2.P$3, RIGHT_LED.+, R_LED_2.P$1, U$1.SLEEVE, U$3.P$6
LEFT1: C204.2 (-), C204.B2 (-), PCB1.A0, R208.2, R208.2A (2), U1.1 (OUT)
LEFT2: C304.2 (-), C304.B2 (-), PCB1.A3, R408.2, R408.2A (2), U2.1 (OUT)
unnamed: C103.+, MAX1044.P$2 (C+)
unnamed: C103.-, MAX1044.P$4 (C-)
unnamed: C204.1 (+), C204.A1 (+), C404.-, C404.-VE (-), R208.1, R208.1A (1), U1.2 (IN-)
unnamed: C403.-, C403.-VE (-), R206.1, R206.1A (1), U1.3 (IN+)
unnamed: PCB1.A5, POT_A5.P$2 (WIPER)
unnamed: LEFT_IN.+, LEFT_IN1.P$1, R204.2, R204.2A (2)
unnamed: LEFT_IN.-, LEFT_IN1.P$2, R202.2, R202.2A (2)
unnamed: C201.1 (+), C201.A1 (+), C402.-, C402.-VE (-), R207.1, R207.1A (1), U1.6 (IN-)
unnamed: C401.-, C401.-VE (-), R205.1, R205.1A (1), U1.5 (IN+)
unnamed: PCB1.D3, R303.1, R303.1A (1)
unnamed: R203.2, R203.2A (2), RIGHT_IN.+, RIGHT_IN1.P$1
unnamed: R201.2, R201.2A (2), RIGHT_IN.-, RIGHT_IN1.P$2
unnamed: PCB1.D2, R304.1, R304.1A (1)
unnamed: LED_2.P$2, R103.1, R103.1A (1), R303.2, R303.2A (2), RIGHT_LED.-
unnamed: LED_1.P$2, LEFT_LED.-, R104.1, R104.1A (1), R304.2, R304.2A (2)
unnamed: PCB1.A2, POT_A4.P$2 (WIPER)
unnamed: C304.1 (+), C304.A1 (+), C503.-, C503.-VE (-), R408.1, R408.1A (1), U2.2 (IN-)
unnamed: C504.-, C504.-VE (-), R406.1, R406.1A (1), U2.3 (IN+)
unnamed: LED1.A, R1.2, R1.2A (2)
unnamed: R102.1, R102.1A (1), R301.2, R301.2A (2), R_LED_2.P$2
unnamed: C301.1 (+), C301.A1 (+), C501.-, C501.-VE (-), R407.1, R407.1A (1), U2.6 (IN-)
unnamed: C502.-, C502.-VE (-), R403.1, R403.1A (1), U2.5 (IN+)
unnamed: R401.2, R401.2A (2), RIGHT_IN_2.P$1
unnamed: L_LED_2.P$2, R101.1, R101.1A (1), R302.2, R302.2A (2)
unnamed: PCB1.D4, R302.1, R302.1A (1)
unnamed: PCB1.D5, R301.1, R301.1A (1)
unnamed: C501.+, C501.+VE (+), R401.1, R401.1A (1)
unnamed: C502.+, C502.+VE (+), R402.1, R402.1A (1)
unnamed: C503.+, C503.+VE (+), R504.1, R504.1A (1)
unnamed: C504.+, C504.+VE (+), R405.1, R405.1A (1)
unnamed: C401.+, C401.+VE (+), R201.1, R201.1A (1)
unnamed: LEFT_IN_2.P$1, R504.2, R504.2A (2)
unnamed: LEFT_IN_2.P$2, R405.2, R405.2A (2)
unnamed: C402.+, C402.+VE (+), R203.1, R203.1A (1)
unnamed: R402.2, R402.2A (2), RIGHT_IN_2.P$2
unnamed: C404.+, C404.+VE (+), R204.1, R204.1A (1)
unnamed: C403.+, C403.+VE (+), R202.1, R202.1A (1)
RIGHT1: C201.2 (-), C201.B2 (-), PCB1.A1, R207.2, R207.2A (2), U1.7 (OUT)
RIGHT2: C301.2 (-), C301.B2 (-), PCB1.A4, R407.2, R407.2A (2), U2.7 (OUT)
VCC: 5V.MP, C101.+, C203.2 (-), C203.B2 (-), C303.2 (-), C303.B2 (-), LED_1.P$3, LED_2.P$3, LEFT_LED.S, L_LED_2.P$3, MAX1044.P$1 (BST), MAX1044.P$8 (V+), PCB1.VIN, POT_A4.P$1 (CCW), POT_A5.P$1 (CCW), POWER_IN.P$1, R1.1, R1.1A (1), RIGHT_LED.S, R_LED_2.P$3, SW6.P$3 (2), SW6.P$4 (2), SW7.P$3 (2), SW7.P$4 (2), SW8.P$3 (2), SW8.P$4 (2), SW9.P$3 (2), SW9.P$4 (2), U1.8 (VCC), U2.8 (VCC), U$1.TIP, U$3.P$5
VEE: C102.-, C202.1 (+), C202.A1 (+), C302.1 (+), C302.A1 (+), MAX1044.P$5 (OUT), U1.4 (VEE), U2.4 (VEE)

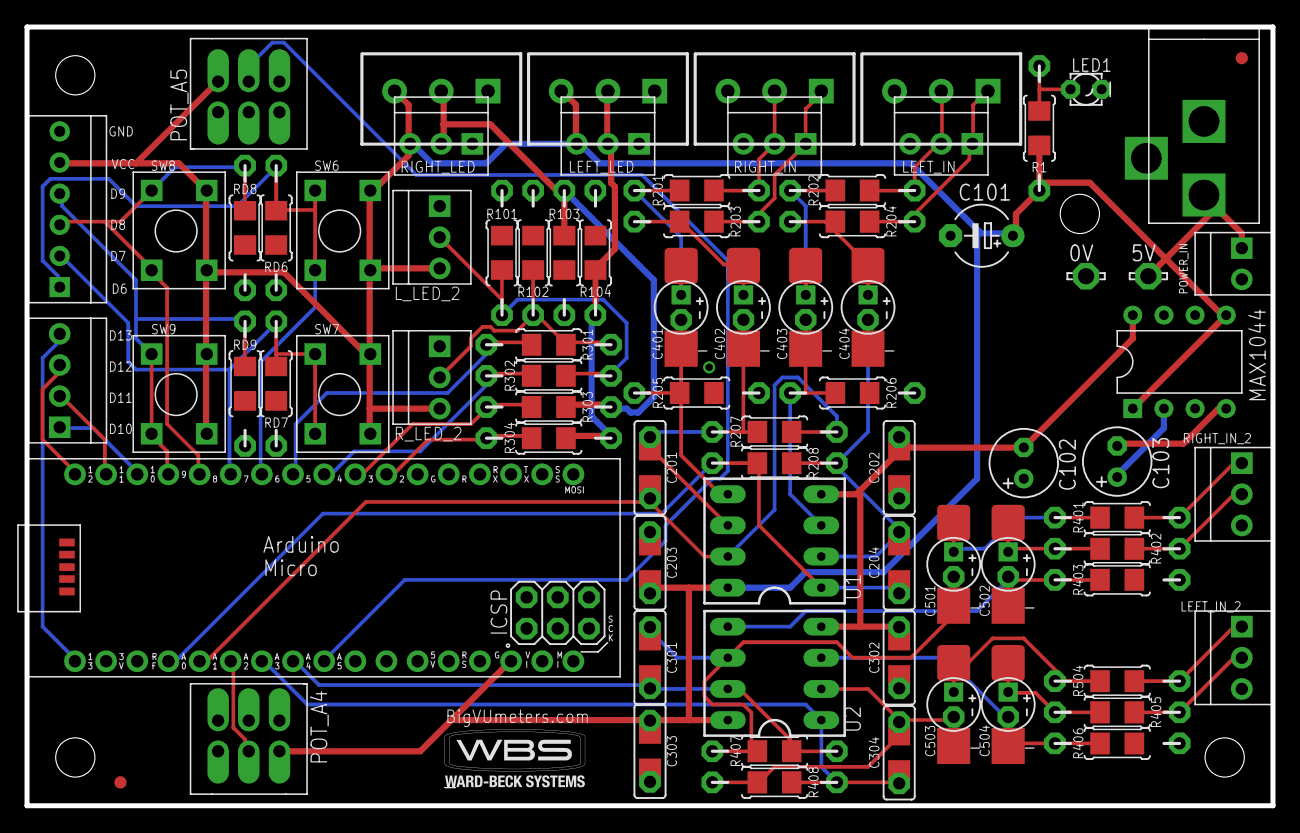
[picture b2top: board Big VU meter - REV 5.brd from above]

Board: 2 copper layers, 101.6 x 63.5 mm, 80 parts (0 on the bottom side), 52 nets.

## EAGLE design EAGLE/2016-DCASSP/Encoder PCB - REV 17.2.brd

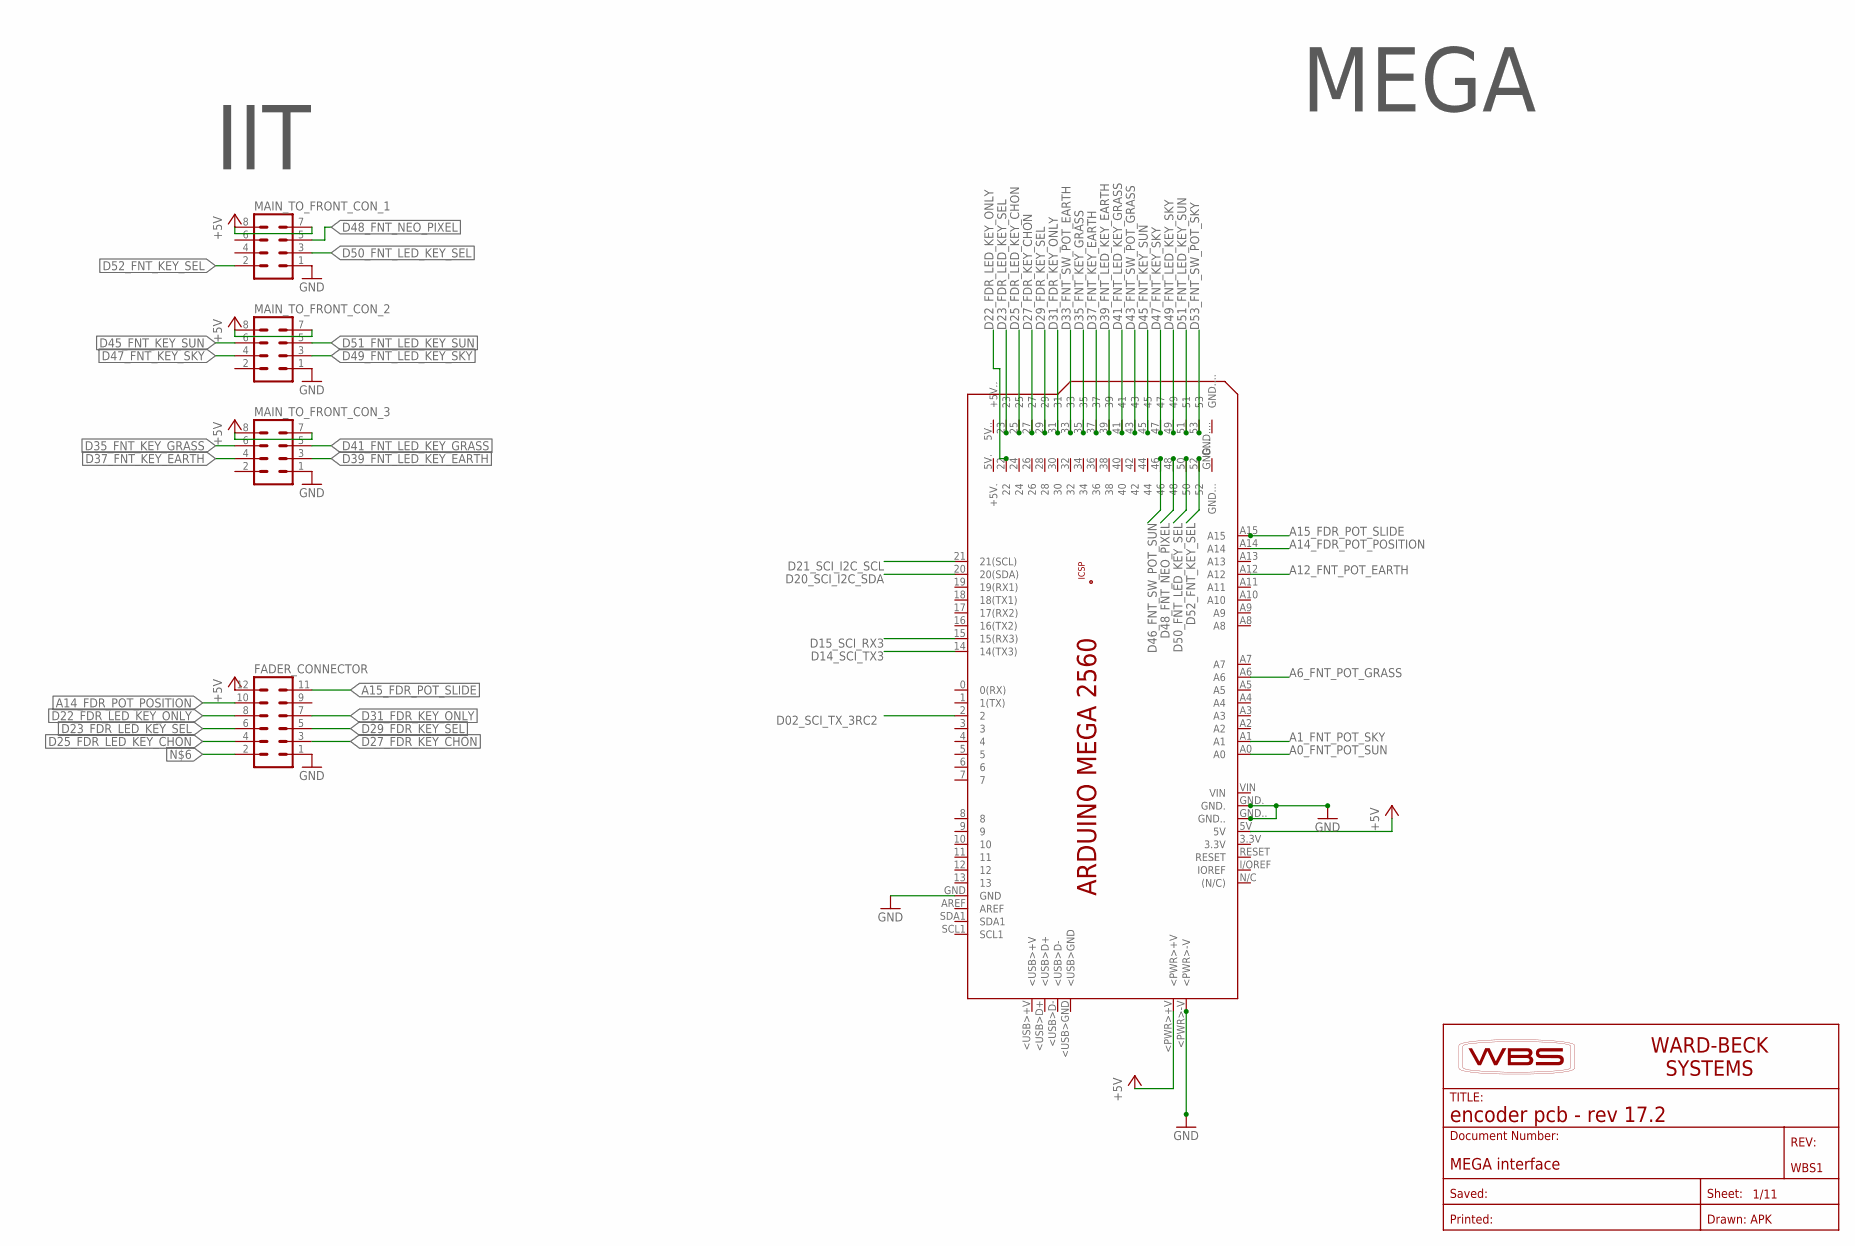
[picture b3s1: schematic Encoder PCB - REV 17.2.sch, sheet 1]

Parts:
FADER_CONNECTOR: MA06-2
MAIN_TO_FRONT_CON_1, MAIN_TO_FRONT_CON_2, MAIN_TO_FRONT_CON_3: MA04-2
PCB1: ARDUINO_MEGA2560
WBS1: MEGA interface; WBS-FRAME_PCB

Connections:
+5V: FADER_CONNECTOR.12, MAIN_TO_FRONT_CON_1.7, MAIN_TO_FRONT_CON_1.8, MAIN_TO_FRONT_CON_2.7, MAIN_TO_FRONT_CON_2.8, MAIN_TO_FRONT_CON_3.7, MAIN_TO_FRONT_CON_3.8, PCB1.5V, PCB1.<PWR>+V; also elsewhere on the board
A0_FNT_POT_SUN: PCB1.A0; also elsewhere on the board
A1_FNT_POT_SKY: PCB1.A1; also elsewhere on the board
A6_FNT_POT_GRASS: PCB1.A6; also elsewhere on the board
A12_FNT_POT_EARTH: PCB1.A12; also elsewhere on the board
A14_FDR_POT_POSITION: FADER_CONNECTOR.10, PCB1.A14; also elsewhere on the board
A15_FDR_POT_SLIDE: FADER_CONNECTOR.11, PCB1.A15; also elsewhere on the board
D02_SCI_TX_3RC2: PCB1.2; also elsewhere on the board
D14_SCI_TX3: PCB1.14 (14(TX3)); also elsewhere on the board
D15_SCI_RX3: PCB1.15 (15(RX3)); also elsewhere on the board
D20_SCI_I2C_SDA: PCB1.20 (20(SDA)); also elsewhere on the board
D21_SCI_I2C_SCL: PCB1.21 (21(SCL)); also elsewhere on the board
D22_FDR_LED_KEY_ONLY: FADER_CONNECTOR.8, PCB1.22; also elsewhere on the board
D23_FDR_LED_KEY_SEL: FADER_CONNECTOR.6, PCB1.23; also elsewhere on the board
D25_FDR_LED_KEY_CHON: FADER_CONNECTOR.4, PCB1.25; also elsewhere on the board
D27_FDR_KEY_CHON: FADER_CONNECTOR.3, PCB1.27; also elsewhere on the board
D29_FDR_KEY_SEL: FADER_CONNECTOR.5, PCB1.29; also elsewhere on the board
D31_FDR_KEY_ONLY: FADER_CONNECTOR.7, PCB1.31; also elsewhere on the board
D33_FNT_SW_POT_EARTH: PCB1.33; also elsewhere on the board
D35_FNT_KEY_GRASS: MAIN_TO_FRONT_CON_3.6, PCB1.35; also elsewhere on the board
D37_FNT_KEY_EARTH: MAIN_TO_FRONT_CON_3.4, PCB1.37; also elsewhere on the board
D39_FNT_LED_KEY_EARTH: MAIN_TO_FRONT_CON_3.3, PCB1.39; also elsewhere on the board
D41_FNT_LED_KEY_GRASS: MAIN_TO_FRONT_CON_3.5, PCB1.41; also elsewhere on the board
D43_FNT_SW_POT_GRASS: PCB1.43; also elsewhere on the board
D45_FNT_KEY_SUN: MAIN_TO_FRONT_CON_2.6, PCB1.45; also elsewhere on the board
D46_FNT_SW_POT_SUN: PCB1.46; also elsewhere on the board
D47_FNT_KEY_SKY: MAIN_TO_FRONT_CON_2.4, PCB1.47; also elsewhere on the board
D48_FNT_NEO_PIXEL: MAIN_TO_FRONT_CON_1.5, PCB1.48; also elsewhere on the board
D49_FNT_LED_KEY_SKY: MAIN_TO_FRONT_CON_2.3, PCB1.49; also elsewhere on the board
D50_FNT_LED_KEY_SEL: MAIN_TO_FRONT_CON_1.3, PCB1.50; also elsewhere on the board
D51_FNT_LED_KEY_SUN: MAIN_TO_FRONT_CON_2.5, PCB1.51; also elsewhere on the board
D52_FNT_KEY_SEL: MAIN_TO_FRONT_CON_1.2, PCB1.52; also elsewhere on the board
D53_FNT_SW_POT_SKY: PCB1.53; also elsewhere on the board
GND: FADER_CONNECTOR.1, MAIN_TO_FRONT_CON_1.1, MAIN_TO_FRONT_CON_2.1, MAIN_TO_FRONT_CON_3.1, PCB1.<PWR>-V, PCB1.GND, PCB1.GND., PCB1.GND..; also elsewhere on the board
unnamed 67: FADER_CONNECTOR.2; also elsewhere on the board

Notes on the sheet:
IIT
MEGA
